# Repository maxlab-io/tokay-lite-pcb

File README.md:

# 

[Tokay Lite](https://maxlab.io/store/edge-ai-camera/) is the ESP32 camera development board ideal for low-power image
processing applications on the edge.

Tokay Lite can be used as standalone devkit to aid developers with a convinient
tool or be embedded in the bigger system to augument it with the vision and
image processing data.

## Tokay Lite Features

* ESP32-S3 chip compatible with TensorFlow Lite, enabling AI right in the device.
* OV2640 camera sensor delivering 15 fps @ 2MP.
* Ultra-low power design: programmable external RTC controls
  the entire power distribution, allowing the device to consume microamps during
  sleep.
* Motion detection with wake-up support.
* Nightvision mode with software-controlled IR filter to improve
  pictures during daytime.
* 10 IR LEDs to illuminate the scene.
* Ambient light sensor to intelligently select between day and night-time modes.
* Convenient 70mm x 70mm form factor.
* Embedded lithium battery charger and JST-PH battery connector.

## PCB Dimensions

Tokay LITE is packed into 70x70mm with M3 mounting holes at each corner,
as can be seen from a following drawing:

## Firmware

The Tokay AI Camera is powered by the ESP-IDF framework.

Check the [GitHub firmware repository]() for the source code
or [the camera documentation page](https://docs.maxlab.io/docs/edge-ai-tokay-lite/firmware/)
for more information on how to build an flash the firmware.

## KiCAD Dependencies

The Tokay PCB is made using [KiML](https://github.com/maxlab-io/kiml/),
the atomic components library from MAXLAB.

If you wish to modify the schematics or PCB you need to install KiML first.
Proceed to [the KiML installation guide](https://github.com/maxlab-io/kiml#how-to-install-kiml)
for further information.

## Ordering Samples

For information about ordering samples please proceed to [MAXLAB Tokay Lite product page](https://maxlab.io/store/edge-ai-camera/).

## License

The project is licensed under [the CERN Open Hardware Licence Version 2 - Permissive](./LICENSE.txt) terms.

## Business Inquiries or Questions

If you have the camera-related questions or inquiries, please drop us an email
on [hi@maxlab.io](mailto:hi@maxlab.io) or send us a message trough
[the Contact Us form](https://maxlab.io/contact/).

## Other Links

* [CADLAB.io](https://cadlab.io/project/27230). 
* [Hackaday](https://hackaday.io/project/189135-tokay-lite-multi-purpose-esp32-ai-camera)

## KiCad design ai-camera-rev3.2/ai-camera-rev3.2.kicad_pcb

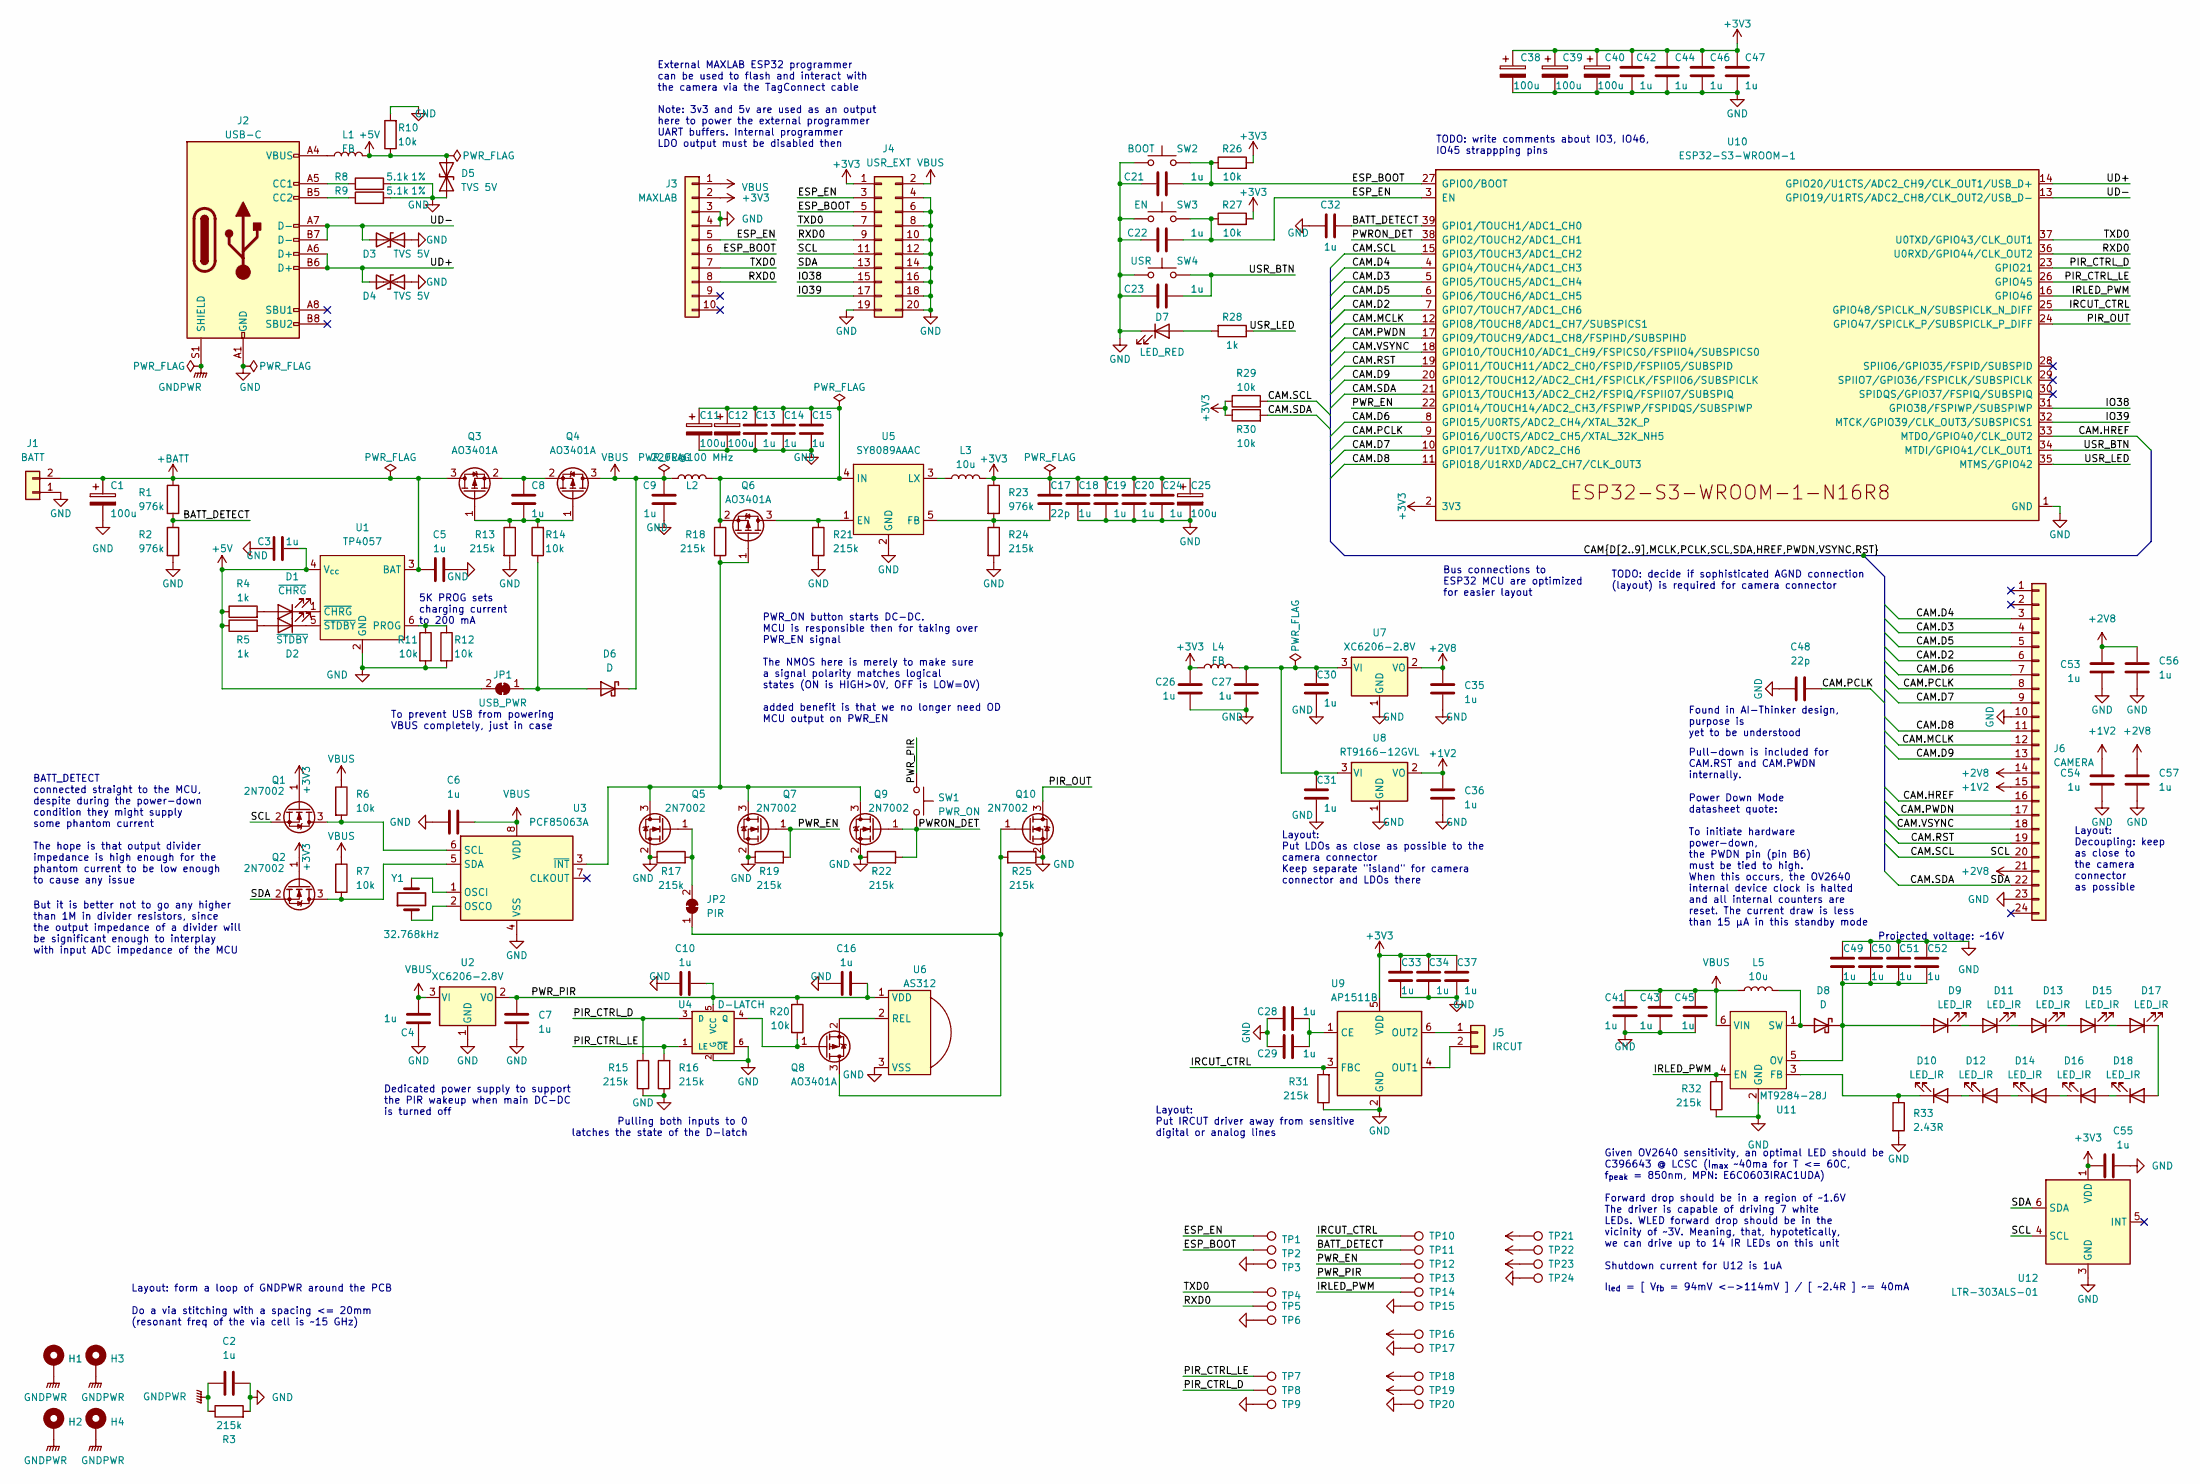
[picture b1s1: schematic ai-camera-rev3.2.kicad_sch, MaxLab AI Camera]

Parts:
C1, C11, C12, C25, C38, C39, C40: 100u_CASE-B-3528_TAJB107K006RNJ; CP_EIA-3528-15_AVX-H; Rating 6.3V; Tolerance 10%; MPN TAJB107K006RNJ
C2, C6, C10, C15, C16, C18, C21, C23, C28, C29, C32, C33, C45, C46, C47, C49, C54, C55, C56, C57: 10u_0402_CL05A105KA5NQNC; C_0402_1005Metric; Tolerance 10%; Rating 25V; MPN CL05A105KA5NQNC
C3, C4, C5, C7, C8, C9, C13, C14, C19, C20, C22, C24, C26, C27, C30, C31, C34, C35, C36, C37, C41, C42, C43, C44, C50, C51, C52, C53: 10u_0402_CL05A105KA5NQNC; C_0402_1005Metric; Rating 25V; Tolerance 10%; MPN CL05A105KA5NQNC
C17, C48: 22p_0402_0402CG220J500NT; C_0402_1005Metric; Rating 50V; Tolerance 5%; MPN 0402CG220J500NT
D1, D7: 0603_RED_KT-0603R; LED_0603_1608Metric; MPN KT-0603R
D2: 0603_GREEN_19-217/GHC-YR1S2/3T; LED_0603_1608Metric; MPN 19-217/GHC-YR1S2/3T
D3, D4, D5: SOD-523_BSD5C051L; D_SOD-523; MPN BSD5C051L
D6, D8: B5819W-SL_SOD-123; D_SOD-123; Rating 1A; MPN B5819W SL
D9, D10, D11, D12, D13, D14, D15, D16, D17, D18: 0603_IR_850nm_E6C0603IRAC1UDA; LED_0603_1608Metric; MPN E6C0603IRAC1UDA
H1, H2, H3, H4: MountingHole_Pad; MountingHole_3.2mm_M3_Pad_TopBottom
J1: Conn-01x02_P2mm_NONAME_JST-PH_C47647; JST_PH_S2B-PH-SM4-TB_1x02-1MP_P2.00mm_Horizontal; MPN C47647
J2: TYPE-C-31-M-12; USB_C_Receptacle_HRO_TYPE-C-31-M-12; MPN TYPE-C-31-M-12
J3: MAXLAB; Tag-Connect_TC2050-IDC-FP_2x05_P1.27mm_Vertical
J4: Conn-02x10_P2.54mm_B-2100S20P-B110; PinHeader_2x10_P2.54mm_Vertical; MPN B-2100S20P-B110
J5: Conn-01x02_P1.25mm_10114829-10102LF; 10114829-10102LF; MPN 10114829-10102LF
J6: Conn_01x24_FFC_0.5mm_AFC01-S24FCC-00; Jushuo_AFC01-S24FCC-00_1x24-1MP_P0.50_Horizontal; MPN AFC01-S24FCC-00
JP1: USB_PWR; SolderJumper-2_P1.3mm_Bridged2Bar_Pad1.0x1.5mm
JP2: PIR; SolderJumper-2_P1.3mm_Bridged2Bar_Pad1.0x1.5mm
L1, L2, L4: FB_2A_0805_220R@100MHz_BLM21PG221SN1D; L_0805_2012Metric_Pad1.15x1.40mm_HandSolder; Rating 2A; MPN BLM21PG221SN1D
L3, L5: 10u_1.5A_4x4mm_SWPA4030S100MT; L_Sunlord_SWPA40xxS; Rating 1.5A; MPN SWPA4030S100MT
Q1, Q2, Q5, Q7, Q9, Q10: 2N7002; SOT-23; MPN 2N7002
Q3, Q4, Q6, Q8: AO3401A; SOT-23; MPN AO3401A
R1, R2, R23: 976k_0402_0402WGD9763TCE; R_0402_1005Metric; Tolerance 0.5%; MPN 0402WGD9763TCE
R3, R13, R15, R16, R17, R18, R19, R21, R22, R24, R25, R31, R32: 215k_0402_0402WGD2153TCE; R_0402_1005Metric; Tolerance 0.5%; MPN 0402WGD2153TCE
R4, R5, R28: 1k_0402_0402WGF1001TCE; R_0402_1005Metric; Tolerance 1%; MPN 0402WGF1001TCE
R6, R7, R10, R11, R12, R14, R20, R26, R27, R29, R30: 10k_0402_0402WGF1002TCE; R_0402_1005Metric; Tolerance 1%; MPN 0402WGF1002TCE
R8, R9: 5.1k_0603_0603WAF5101T5E; R_0603_1608Metric; Tolerance 1%; MPN 0603WAF5101T5E
R33: 2.43R_0805_0805W8F243KT5E; R_0805_2012Metric; Tolerance 1%; MPN 0805W8F243KT5E
SW1, SW4: SW_PB_90deg_K2-1102AQ-H4CW-01; MPN K2-1102AQ-N4CW-01
SW2, SW3: SW_PB_TS-1187A-B-A-B; SW_SPST_TL3342; MPN TS-1187A-B-A-B
TP1, TP2, TP3, TP4, TP5, TP6, TP7, TP8, TP9, TP10, TP11, TP12, TP13, TP14, TP15, TP16, TP17, TP18, TP19, TP20, TP21, TP22, TP23, TP24: TestPoint; TestPoint_Pad_D1.0mm
U1: TP4057-42-SOT26-R; SOT-23-6; MPN TP4057-42-SOT26-R
U2, U7: XC6206-2.8V; SOT-23; MPN XC6206-2.8V
U3: PCF85063AT; SO-8_3.9x4.9mm_P1.27mm; MPN PCF85063AT/AAZ
U4: TI_SN74LVC1G373DBVR; SOT-23-6; MPN SN74LVC1G373DBVR
U5: SY8089AAAC; SOT-23-5; MPN SY8089AAAC
U6: PIR_AS312; AS312; MPN AS312
U8: RT9166-12GVL; SOT-23; MPN RT9166-12GVL
U9: AP1511B; SOT-23-6; MPN AP1511B
U10: ESP32-S3-WROOM-1-N16R8; ESP32-S3-WROOM-1; MPN ESP32-S3-WROOM-1-N16R8
U11: MT9284-28J; SOT-23-6; MPN MT9284-28J
U12: LTR-303ALS-01; Lite-On_LTR-303ALS-01; MPN LTR-303ALS-01
Y1: 32.768kHz_Q13FC1350000400; Crystal_SMD_3215-2Pin_3.2x1.5mm; MPN Q13FC1350000400

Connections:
+1V2: C36.1, C54.2, J6.15, TP16.1, U8.2 (VO)
+2V8: C35.1, C53.1, C56.2, C57.2, J6.14, J6.21, TP18.1, U7.2 (VO)
+3V3: C17.1, C18.2, C19.2, C20.2, C24.2, C25.1, C26.1, C33.2, C34.2, C37.2, C38.1, C39.1, C40.1, C42.1, C44.1, C46.1, C47.1, C55.1, J3.2, J4.1, L3.2, L4.1, Q1.1 (G), Q2.1 (G), R23.1, R26.2, R27.2, R29.1, R30.1, TP22.1, U9.5 (VDD), U10.2 (3V3), U12.1 (VDD)
+5V: C3.2, D5.2 (A2), JP1.2 (B), L1.2, R4.1, R5.1, R10.1, TP23.1, U1.4 (V_{cc})
+BATT: C1.1, C5.1, J1.2, Q3.3 (D), R1.1, TP19.1, U1.3 (BAT)
/BATT_DETECT: C32.1, R1.2, R2.1, TP11.1, U10.39 (GPIO1/TOUCH1/ADC1_CH0)
/CAM.D2: J6.6, U10.7 (GPIO7/TOUCH7/ADC1_CH6)
/CAM.D3: J6.4, U10.5 (GPIO5/TOUCH5/ADC1_CH4)
/CAM.D4: J6.3, U10.4 (GPIO4/TOUCH4/ADC1_CH3)
/CAM.D5: J6.5, U10.6 (GPIO6/TOUCH6/ADC1_CH5)
/CAM.D6: J6.7, U10.8 (GPIO15/U0RTS/ADC2_CH4/XTAL_32K_P)
/CAM.D7: J6.9, U10.10 (GPIO17/U1TXD/ADC2_CH6)
/CAM.D8: J6.11, U10.11 (GPIO18/U1RXD/ADC2_CH7/CLK_OUT3)
/CAM.D9: J6.13, U10.20 (GPIO12/TOUCH12/ADC2_CH1/FSPICLK/FSPIIO6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)
/CAM.HREF: J6.16, U10.33 (MTDO/GPIO40/CLK_OUT2)
/CAM.MCLK: J6.12, U10.12 (GPIO8/TOUCH8/ADC1_CH7/SUBSPICS1)
/CAM.PCLK: C48.1, J6.8, U10.9 (GPIO16/U0CTS/ADC2_CH5/XTAL_32K_NH5)
/CAM.PWDN: J6.17, U10.17 (GPIO9/TOUCH9/ADC1_CH8/FSPIHD/SUBSPIHD)
/CAM.RST: J6.19, U10.19 (GPIO11/TOUCH11/ADC2_CH0/FSPID/FSPIIO5/S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)
/CAM.SCL: J4.11, J6.20, Q1.2 (S), R29.2, U10.15 (GPIO3/TOUCH3/ADC1_CH2), U12.4 (SCL)
/CAM.SDA: J4.13, J6.22, Q2.2 (S), R30.2, U10.21 (GPIO13/TOUCH13/ADC2_CH2/FSPIQ/FSPIIO7/S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), U12.6 (SDA)
/CAM.VSYNC: J6.18, U10.18 (GPIO10/TOUCH10/ADC1_CH9/FSPICS0/FSPIIO4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)
/ESP_BOOT: C21.2, J3.6, J4.5, R26.1, SW2.2, TP2.1, U10.27 (GPIO0/BOOT)
/ESP_EN: C22.2, J3.5, J4.3, R27.1, SW3.2, TP1.1, U10.3 (EN)
/IO38: J4.15, U10.31 (GPIO38/FSPIWP/SUBSPIWP)
/IO39: J4.17, U10.32 (MTCK/GPIO39/CLK_OUT3/SUBSPICS1)
/IRCUT_CTRL: R31.2, TP10.1, U9.3 (FBC), U10.25 (GPIO48/SPICLK_N/SUBSPICLK_N_DIFF)
/IRLED_PWM: R32.2, TP14.1, U10.16 (GPIO46), U11.4 (EN)
/PIR_CTRL_D: R15.2, TP8.1, U4.3 (D), U10.23 (GPIO21)
/PIR_CTRL_LE: R16.2, TP7.1, U4.1 (LE), U10.26 (GPIO45)
/PIR_OUT: Q10.3 (D), U10.24 (GPIO47/SPICLK_P/SUBSPICLK_P_DIFF)
/PWRON_DET: Q9.1 (G), R22.2, SW1.2, U10.38 (GPIO2/TOUCH2/ADC1_CH1)
/PWR_EN: Q7.1 (G), R19.2, TP12.1, U10.22 (GPIO14/TOUCH14/ADC2_CH3/FSPIWP/FSPIDQS/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)
/PWR_PIR: C7.1, C10.1, C16.1, R20.1, SW1.1, TP13.1, U2.2 (VO), U4.5 (VCC), U6.1 (VDD)
/RXD0: J3.8, J4.9, TP5.1, U10.36 (U0RXD/GPIO44/CLK_OUT2)
/TXD0: J3.7, J4.7, TP4.1, U10.37 (U0TXD/GPIO43/CLK_OUT1)
/UD+: D4.2 (A2), J2.A6 (D+), J2.B6 (D+), U10.14 (GPIO20/U1CTS/ADC2_CH9/CLK_OUT1/USB_D+)
/UD-: D3.2 (A2), J2.A7 (D-), J2.B7 (D-), U10.13 (GPIO19/U1RTS/ADC2_CH8/CLK_OUT2/USB_D-)
/USR_BTN: C23.2, SW4.2, U10.34 (MTDI/GPIO41/CLK_OUT1)
/USR_LED: R28.1, U10.35 (MTMS/GPIO42)
GND: C1.2, C2.1, C3.1, C4.1, C5.2, C6.2, C7.2, C9.1, C10.2, C11.2, C12.2, C13.1, C14.2, C15.1, C16.2, C18.1, C19.1, C20.1, C21.1, C22.1, C23.1, C24.1, C25.2, C26.2, C27.2, C28.2, C29.2, C30.2, C31.2, C32.2, C33.1, C34.1, C35.2, C36.2, C37.1, C38.2, C39.2, C40.2, C41.1, C42.2, C43.2, C44.2, C45.1, C46.2, C47.2, C48.2, C49.2, C50.1, C51.1, C52.1, C53.2, C54.1, C55.2, C56.1, C57.1, D3.1 (A1), D4.1 (A1), D5.1 (A1), D7.1 (K), J1.1, J2.A1 (GND), J2.A12 (GND), J2.B1 (GND), J2.B12 (GND), J3.3, J3.4, J4.4, J4.6, J4.8, J4.10, J4.12, J4.14, J4.16, J4.18, J4.19, J4.20, J6.10, J6.23, Q5.2 (S), Q7.2 (S), Q9.2 (S), Q10.2 (S), R2.2, R3.2, R8.2, R9.2, R10.2, R11.2, R12.2, R13.2, R15.1, R16.1, R17.1, R19.1, R21.2, R22.1, R24.2, R25.1, R31.1, R32.1, R33.2, SW2.1, SW3.1, SW4.1, TP3.1, TP6.1, TP9.1, TP15.1, TP17.1, TP20.1, TP24.1, U1.2 (GND), U2.1 (GND), U3.4 (VSS), U4.2 (G), U4.6 (~OE), U5.2 (GND), U6.3 (VSS), U7.1 (GND), U8.1 (GND), U9.2 (GND), U10.1 (GND), U10.40 (GND), U10.41 (GND), U11.2 (GND), U12.3 (GND)
GNDPWR: C2.2, H1.1, H2.1, H3.1, H4.1, J2.S1 (SHIELD), R3.1
unnamed: D1.2 (A), R4.2
unnamed: D1.1 (K), U1.1 (~CHRG)
unnamed: D2.2 (A), R5.2
unnamed: D2.1 (K), U1.5 (~STDBY)
unnamed: D6.2 (A), JP1.1 (A), R14.1
unnamed: D7.2 (A), R28.2
unnamed: D8.2 (A), L5.2, U11.1 (SW)
unnamed: C49.1, C50.2, C51.2, C52.2, D8.1 (K), D9.2 (A), U11.5 (OV)
unnamed: D10.2 (A), D12.1 (K)
unnamed: D10.1 (K), R33.1, U11.3 (FB)
unnamed: D9.1 (K), D11.2 (A)
unnamed: D11.1 (K), D13.2 (A)
unnamed: D12.2 (A), D14.1 (K)
unnamed: D13.1 (K), D15.2 (A)
unnamed: D14.2 (A), D16.1 (K)
unnamed: D15.1 (K), D17.2 (A)
unnamed: D16.2 (A), D18.1 (K)
unnamed: D17.1 (K), D18.2 (A)
unnamed: J2.A5 (CC1), R8.1
unnamed: J2.B5 (CC2), R9.1
unnamed: J2.A4 (VBUS), J2.A9 (VBUS), J2.B4 (VBUS), J2.B9 (VBUS), L1.1
unnamed: J5.1, U9.6 (OUT2)
unnamed: J5.2, U9.4 (OUT1)
unnamed: JP2.1 (A), Q8.3 (D), Q10.1 (G), R25.2
unnamed: JP2.2 (B), Q5.1 (G), R17.2
unnamed: Q1.3 (D), R6.2, U3.6 (SCL)
unnamed: Q2.3 (D), R7.2, U3.5 (SDA)
unnamed: C8.1, Q3.1 (G), Q4.1 (G), R13.1, R14.2
unnamed: C8.2, Q3.2 (S), Q4.2 (S)
unnamed: Q5.3 (D), Q6.1 (G), Q7.3 (D), Q9.3 (D), R18.2, U3.3 (~INT)
unnamed: Q6.3 (D), R21.1, U5.1 (EN)
unnamed: C11.1, C12.1, C13.2, C14.1, C15.2, L2.2, Q6.2 (S), R18.1, U5.4 (IN)
unnamed: Q8.1 (G), R20.2, U4.4 (Q)
unnamed: Q8.2 (S), U6.2 (REL)
unnamed: R11.1, R12.1, U1.6 (PROG)
unnamed: U3.1 (OSCI), Y1.2
unnamed: U3.2 (OSCO), Y1.1
unnamed: C17.2, R23.2, R24.1, U5.5 (FB)
unnamed: L3.1, U5.3 (LX)
unnamed: C27.1, C30.1, C31.1, L4.2, U7.3 (VI), U8.3 (VI)
unnamed: C28.1, C29.1, U9.1 (CE)
VBUS: C4.2, C6.1, C9.2, C41.2, C43.1, C45.2, D6.1 (K), J3.1, J4.2, L2.1, L5.1, Q4.3 (D), R6.1, R7.1, TP21.1, U2.3 (VI), U3.8 (VDD), U11.6 (VIN)

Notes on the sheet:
Found in AI-Thinker design, purpose is yet to be understood
External MAXLAB ESP32 programmer can be used to flash and interact with the camera via the TagConnect cable
I_{led} = [ V_{fb} = 94mV <->114mV ] / [ ~2.4R ] ~= 40mA
But it is better not to go any higher than 1M in divider resistors, since the output impedance of a divider will be significant enough to interplay with input ADC impedance of the MCU
Pulling both inputs to 0 latches the state of the D-latch
Note: 3v3 and 5v are used as an output here to power the external programmer UART buffers. Internal programmer LDO output must be disabled then
Layout: Put IRCUT driver away from sensitive digital or analog lines
Layout: form a loop of GNDPWR around the PCB Do a via stitching with a spacing <= 20mm (resonant freq of the via cell is ~15 GHz)
Pull-down is included for CAM.RST and CAM.PWDN internally.
TODO: write comments about IO3, IO46, IO45 strappping pins
Bus connections to ESP32 MCU are optimized for easier layout
To prevent USB from powering VBUS completely, just in case
PWR_ON button starts DC-DC. MCU is responsible then for taking over PWR_EN signal The NMOS here is merely to make sure a signal polarity matches logical states (ON is HIGH>0V, OFF is LOW=0V) added benefit is that we no longer need OD MCU output on PWR_EN
Power Down Mode datasheet quote: To initiate hardware power-down, the PWDN pin (pin B6) must be tied to high. When this occurs, the OV2640 internal device clock is halted and all internal counters are reset. The current draw is less than 15 µA in this standby mode
Layout: Put LDOs as close as possible to the camera connector Keep separate "island" for camera connector and LDOs there
TODO: decide if sophisticated AGND connection (layout) is required for camera connector
5K PROG sets charging current to 200 mA
Given OV2640 sensitivity, an optimal LED should be C396643 @ LCSC (I_{max} ~40ma for T <= 60C, f_{peak} = 850nm, MPN: E6C0603IRAC1UDA) Forward drop should be in a region of ~1.6V The driver is capable of driving 7 white LEDs. WLED forward drop should be in the vicinity of ~3V. Meaning, that, hypote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
BATT_DETECT connected straight to the MCU, despite during the power-down condition they might supply some phantom current The hope is that output divider impedance is high enough for the phantom current to be low enough to cause any issue
Dedicated power supply to support the PIR wakeup when main DC-DC is turned off
Projected voltage: ~16V
Layout: Decoupling: keep as close to the camera connector as possible

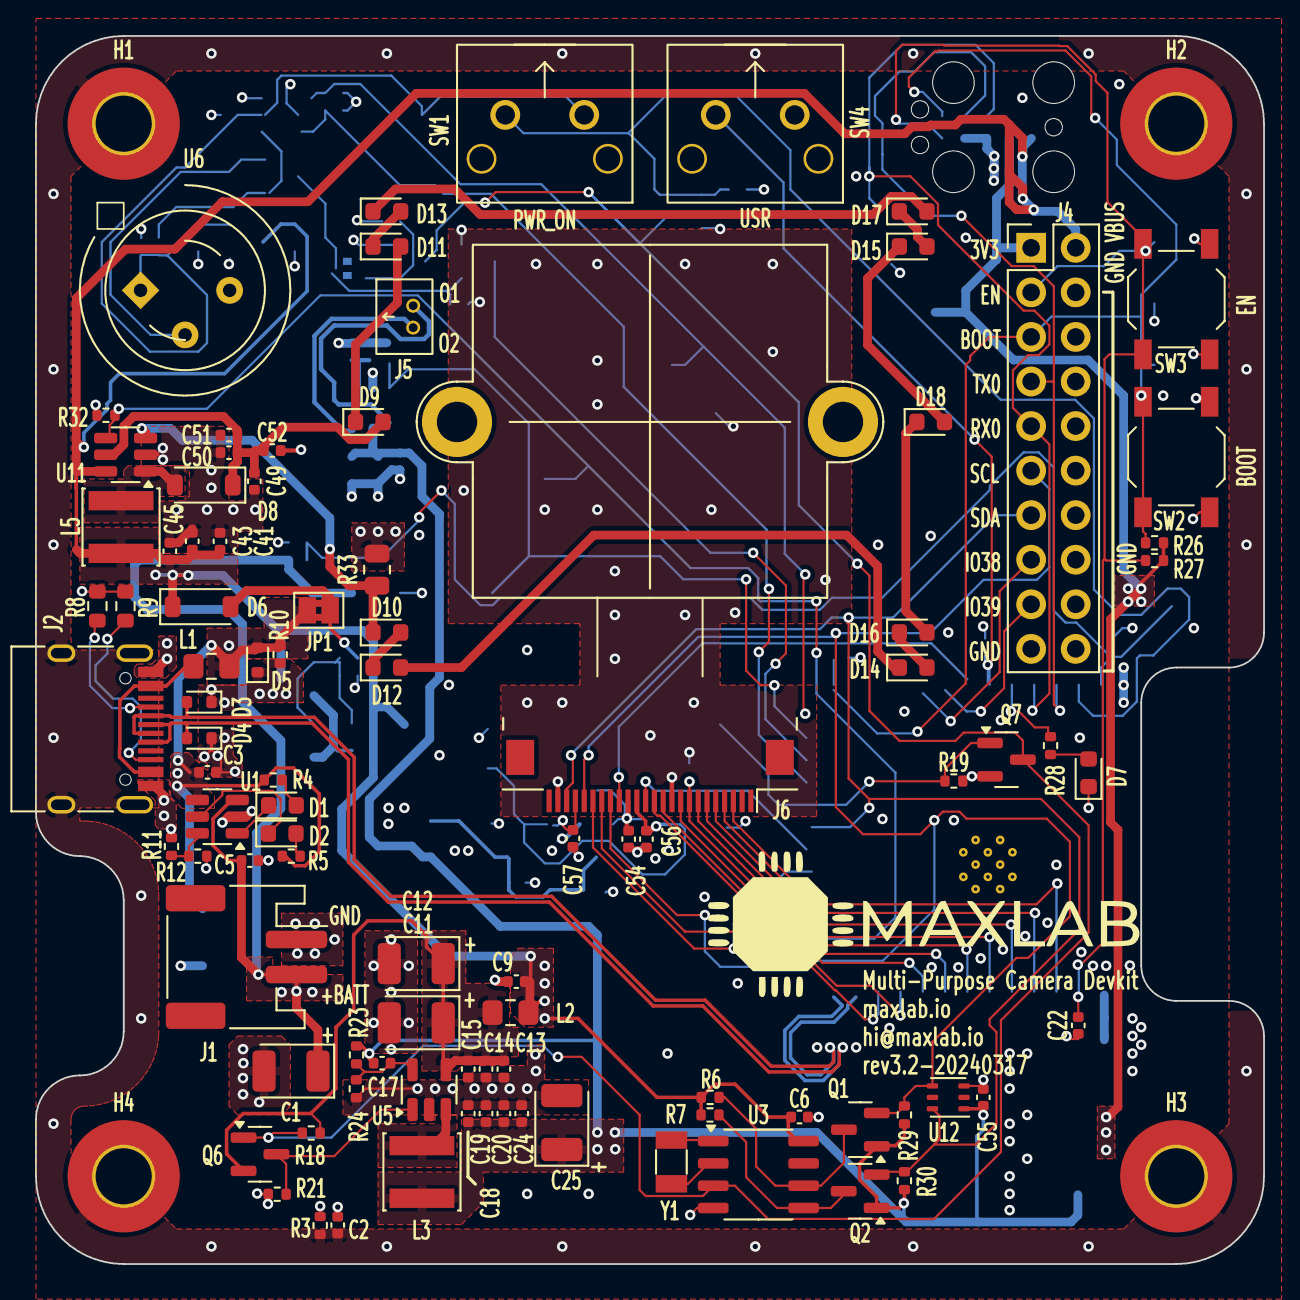
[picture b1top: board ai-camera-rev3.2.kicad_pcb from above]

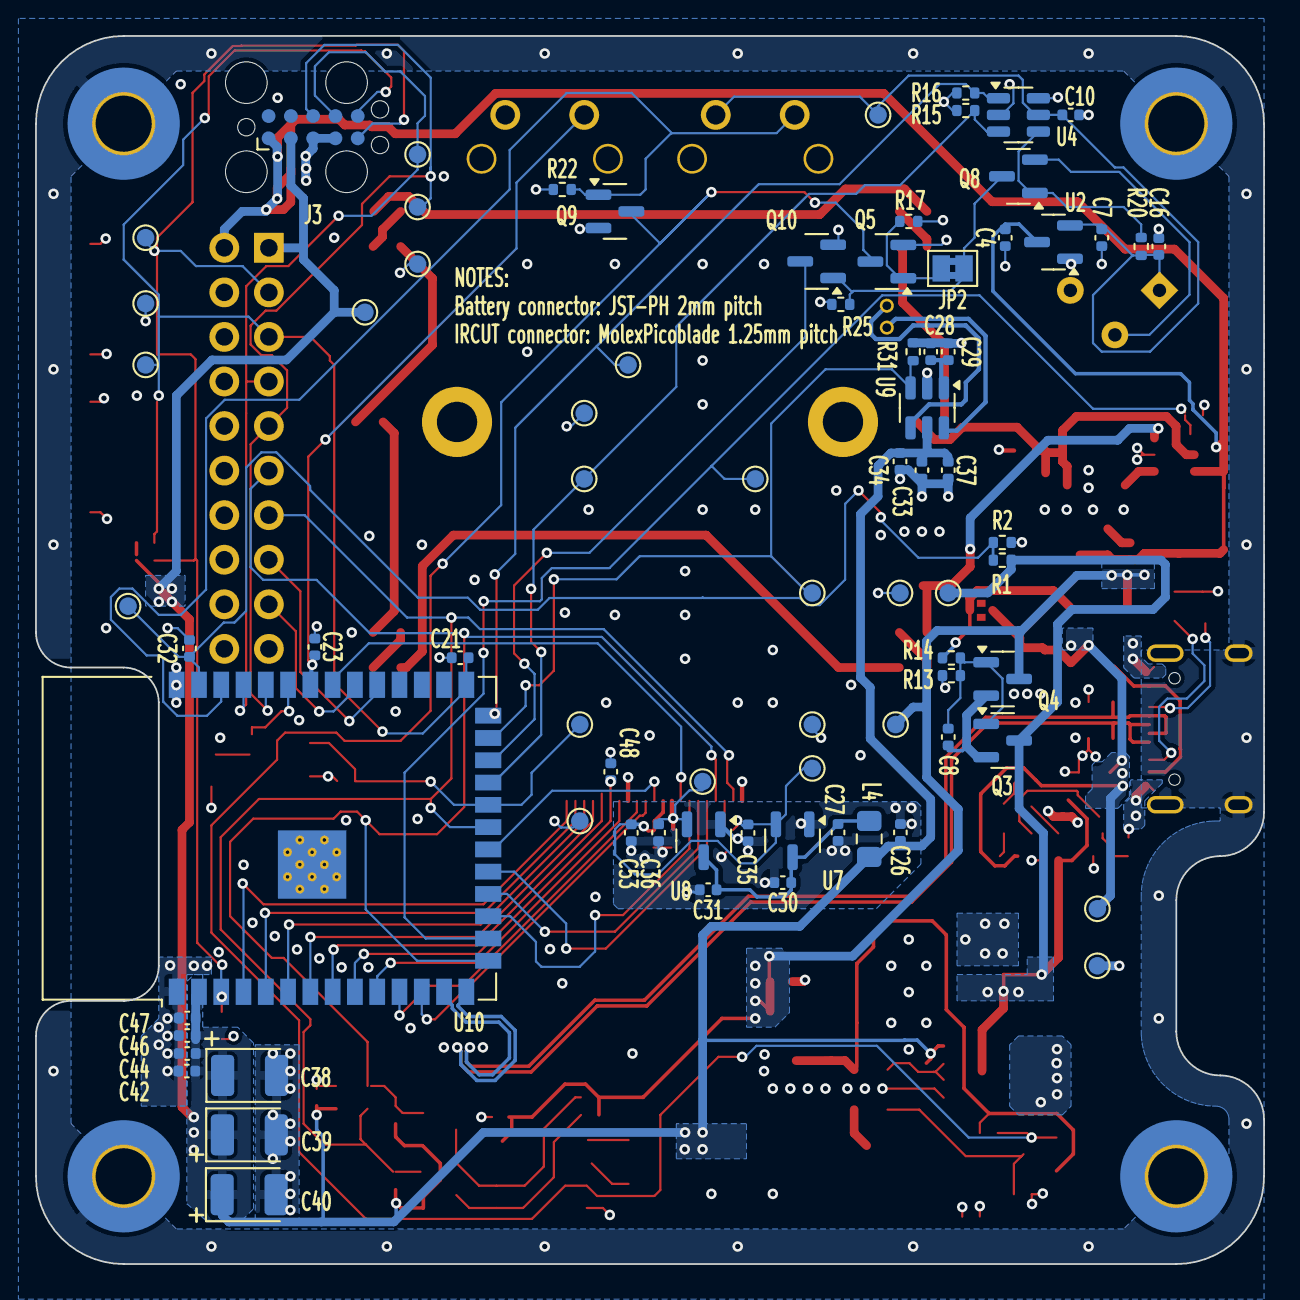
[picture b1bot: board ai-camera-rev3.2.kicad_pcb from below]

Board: 4 copper layers, 70.0 x 70.0 mm, 176 parts (78 on the bottom side), 84 nets.

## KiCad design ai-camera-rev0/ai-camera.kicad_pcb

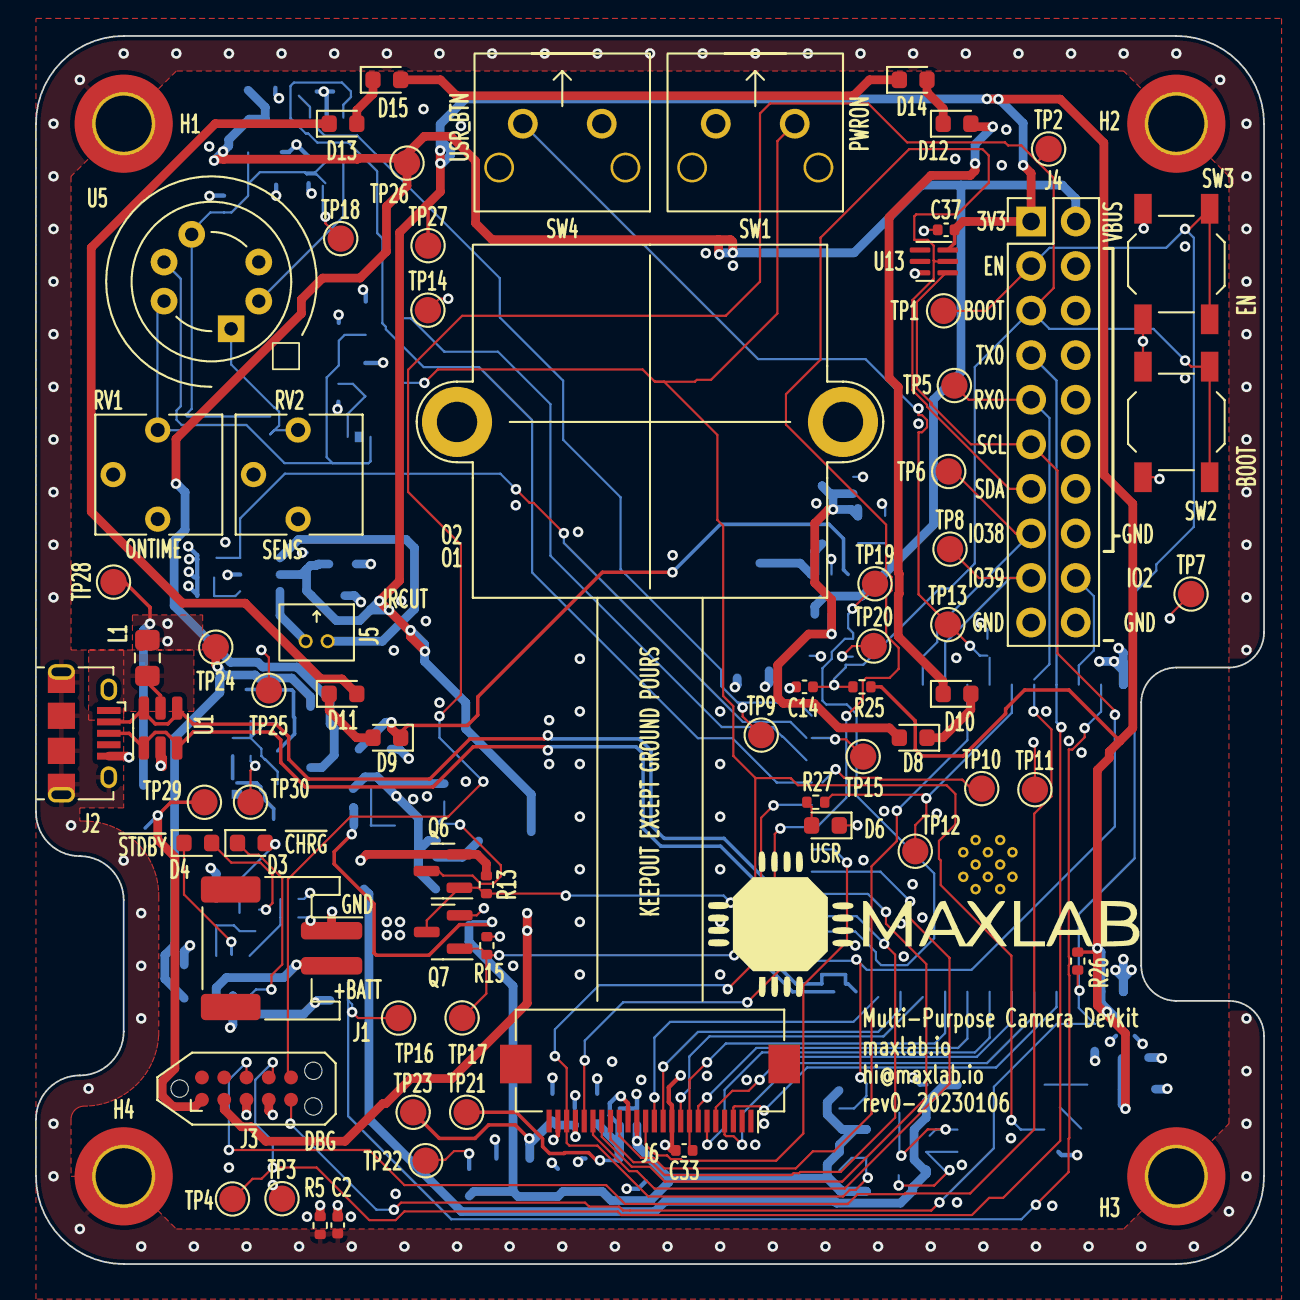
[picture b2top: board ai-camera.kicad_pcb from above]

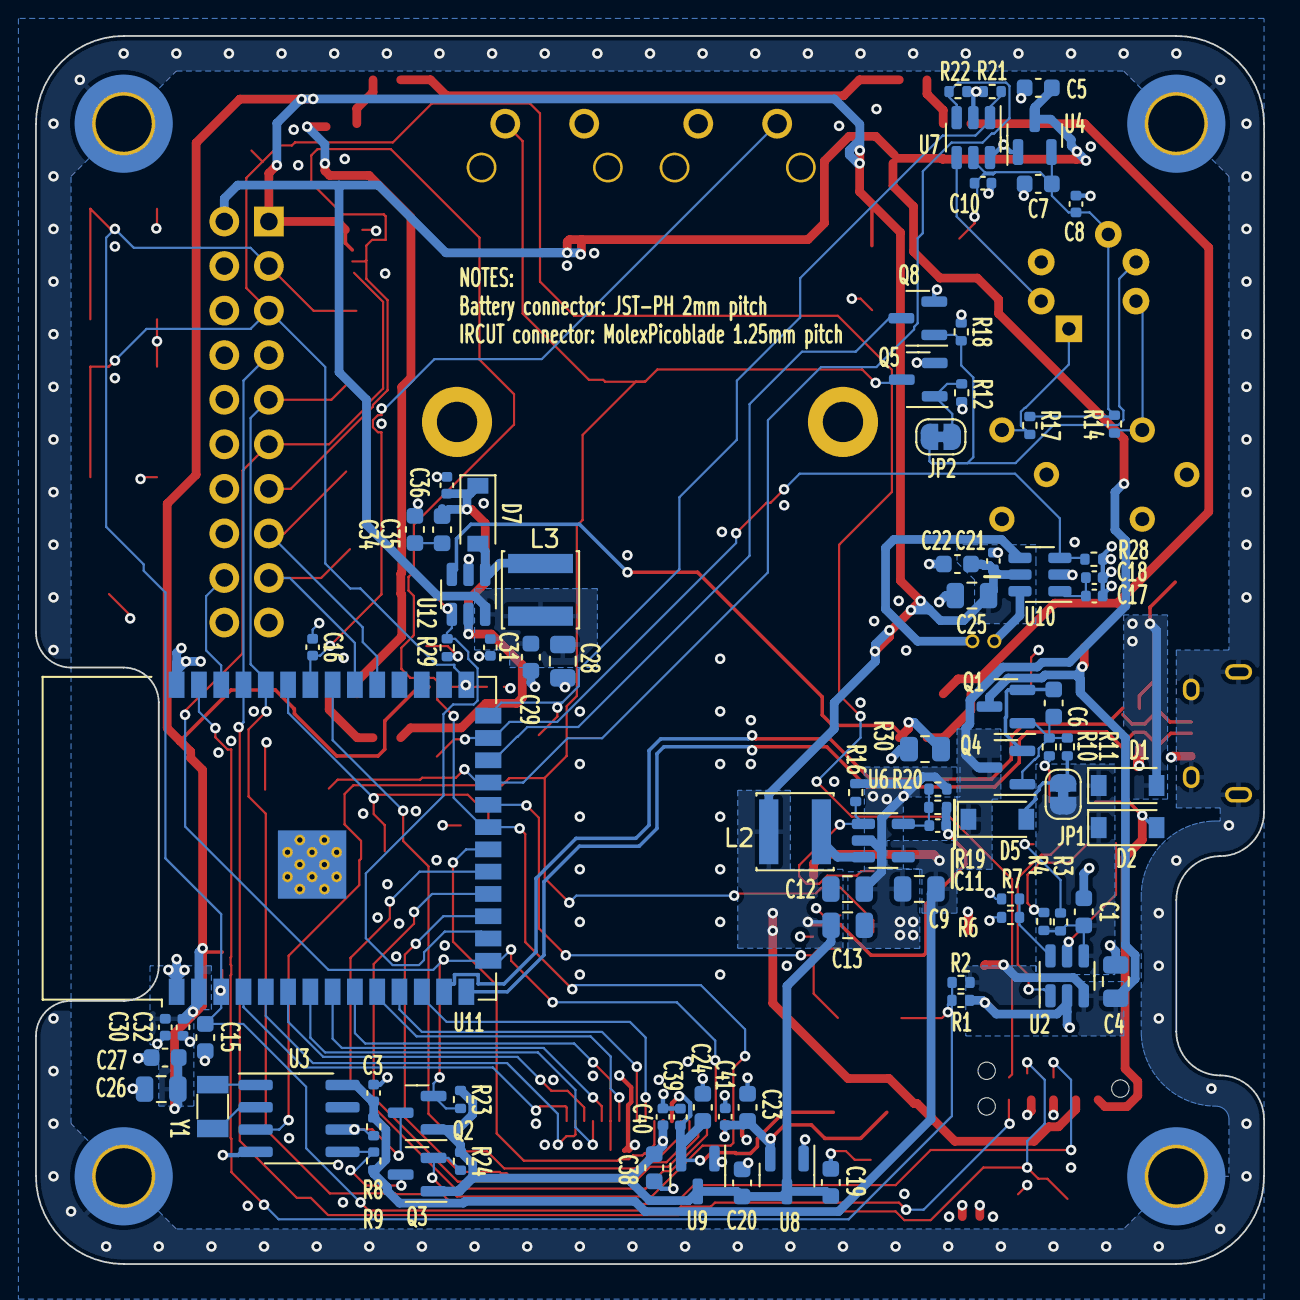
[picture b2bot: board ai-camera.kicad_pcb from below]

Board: 4 copper layers, 70.0 x 70.0 mm, 159 parts (86 on the bottom side), 82 nets.

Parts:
C1, C5, C6, C7, C15, C19, C20, C22, C23, C24, C27, C29, C34, C35, C38: 10u_0603_CL10A106MA8NRNC; C_0603_1608Metric
C2, C3, C8, C10, C14, C16, C17, C18, C21, C30, C31, C32, C36, C37, C39, C40, C41: 100n_0402_CL05B104KB54PNC; C_0402_1005Metric
C4, C9, C12, C13, C25, C26, C28: 22u_0805_CL21A226MAQNNNE; C_0805_2012Metric
C11, C33: 22p_0402_0402CG220J500NT; C_0402_1005Metric
D1, D2, D5, D7: B5819W-SL_SOD-123; D_SOD-123
D3, D6: 0603_RED_KT-0603R; LED_0603_1608Metric
D4: 0603_GREEN_19-217/GHC-YR1S2/3T; LED_0603_1608Metric
D8, D9, D10, D11, D12, D13, D14, D15: 0603_IR_850nm_E6C0603IRAC1UDA; LED_0603_1608Metric
H1, H2, H3, H4: M3; MountingHole_3.2mm_M3_DIN965_Pad_TopBottom
J1: Conn-01x02_P2mm_NONAME_JST-PH_C47647; JST_PH_S2B-PH-SM4-TB_1x02-1MP_P2.00mm_Horizontal
J2: USB_B_Micro_10118194-0001LF; USB_Micro-B_Amphenol_10118194_Horizontal
J3: DBG; Tag-Connect_TC2050-IDC-NL_2x05_P1.27mm_Vertical
J4: Conn-02x10_P2.54mm_B-2100S20P-B110; PinHeader_2x10_P2.54mm_Vertical
J5: Conn-01x02_P1.25mm_10114829-10102LF; 10114829-10102LF
J6: Conn_01x24_FFC_0.5mm_hirose_FH12-24S-0.5SH; Hirose_FH12-24S-0.5SH_1x24-1MP_P0.50mm_Horizontal
JP1: CUT_USB; SolderJumper-2_P1.3mm_Bridged_RoundedPad1.0x1.5mm
JP2: CUT_PIR; SolderJumper-2_P1.3mm_Bridged_RoundedPad1.0x1.5mm
L1: 0805_FB_220R@100MHz_BLM21PG221SN1D; L_0805_2012Metric_Pad1.15x1.40mm_HandSolder
L2, L3: 10u_SWPA4030S100MT; L_Sunlord_SWPA40xxS
Q1, Q4, Q6: AO3401A; SOT-23
Q2, Q3, Q5, Q7, Q8: AO3400A; SOT-23
R1, R2, R14, R17, R19: 976k_0402_0402WGD9763TCE; R_0402_1005Metric
R3, R4, R27: 1k_0402_0402WGF1001TCE; R_0402_1005Metric
R5, R10, R12, R13, R15, R16, R18, R20, R21, R22, R28, R29: 215k_0402_0402WGD2153TCE; R_0402_1005Metric
R6, R7, R8, R9, R11, R23, R24, R25, R26: 10k_0402_0402WGF1002TCE; R_0402_1005Metric
R30: 2.5R_0805_AR05FTCW2R50; R_0805_2012Metric
RV1, RV2: 1M_3362P-1-105; Potentiometer_Vishay_T73YP_Vertical
SW1, SW4: SW_PB_90deg_K2-1102AQ-H4CW-01
SW2, SW3: SW_PB_TS-1187A-B-A-B; SW_SPST_TL3342
TP1, TP2, TP3, TP4, TP5, TP6, TP7, TP8, TP9, TP10, TP11, TP12, TP13, TP14, TP15, TP16, TP17, TP18, TP19, TP20, TP21, TP22, TP23, TP24, TP25, TP26, TP27, TP28, TP29, TP30: TP; TestPoint_Pad_D1.5mm
U1: SRV05-4; SOT-23-6
U2: TP4057-42-SOT26-R; SOT-23-6
U3: PCF8563T/5,518; SOIC-8_3.9x4.9mm_P1.27mm
U4, U8: XC6206-2.8V; SOT-23
U5: PIR_BS612; BS612
U6: SY8089AAAC; SOT-23-5
U7: SOT-23-6_SN74LVC1G373DBVR_TI; SOT-23-6
U9: RT9166-12GVL; SOT-23
U10: AP1511B; SOT-23-6
U11: ESP32-S3-WROOM-1-N16R8; ESP32-S3-WROOM-1
U12: MT9284-28J; SOT-23-6
U13: APDS-9306-065; Broadcom_DFN-6_2x2mm_P0.65mm
Y1: 32.768kHz_Q13FC1350000400; Crystal_SMD_3215-2Pin_3.2x1.5mm

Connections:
+1V2: C24.1, C39.2, J6.15, TP21.1, U9.2 (VO)
+2V8: C23.1, C41.2, J6.21, TP23.1, U8.2 (VO)
+3V3: C11.1, C12.1, C13.1, C19.1, C20.1, C21.2, C22.2, C25.2, C26.1, C27.1, C30.1, C32.1, C37.1, C38.1, C40.2, J3.2, J4.1, J6.14, L2.2, Q2.1 (G), Q3.1 (G), R19.1, R23.1, R24.1, R25.2, R26.2, TP27.1, U8.3 (VI), U9.3 (VI), U10.5 (VDD), U11.2 (3V3), U13.3 (VDD)
+5F: D1.2 (A), L1.2, TP28.1
+5P: D2.2 (A), J3.1, TP29.1
+BATT: C4.1, J1.2, Q1.3 (D), R1.1, TP24.1, U2.3 (BAT)
/BATT_DETECT: R1.2, R2.1, TP16.1, U11.39 (GPIO1/TOUCH1/ADC1_CH0)
/CAM.D2: J6.6, U11.7 (GPIO7/TOUCH7/ADC1_CH6)
/CAM.D3: J6.4, U11.5 (GPIO5/TOUCH5/ADC1_CH4)
/CAM.D4: J6.3, U11.4 (GPIO4/TOUCH4/ADC1_CH3)
/CAM.D5: J6.5, U11.6 (GPIO6/TOUCH6/ADC1_CH5)
/CAM.D6: J6.7, U11.8 (GPIO15/U0RTS/ADC2_CH4/XTAL_32K_P)
/CAM.D7: J6.9, U11.10 (GPIO17/U1TXD/ADC2_CH6)
/CAM.D8: J6.11, U11.11 (GPIO18/U1RXD/ADC2_CH7/CLK_OUT3)
/CAM.D9: J6.13, U11.20 (GPIO12/TOUCH12/ADC2_CH1/FSPICLK/FSPIIO6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)
/CAM.HREF: J6.16, U11.33 (MTDO/GPIO40/CLK_OUT2)
/CAM.MCLK: J6.12, U11.12 (GPIO8/TOUCH8/ADC1_CH7/SUBSPICS1)
/CAM.PCLK: C33.1, J6.8, U11.9 (GPIO16/U0CTS/ADC2_CH5/XTAL_32K_NH5)
/CAM.PWDN: J6.17, U11.17 (GPIO9/TOUCH9/ADC1_CH8/FSPIHD/SUBSPIHD)
/CAM.RST: J6.19, U11.19 (GPIO11/TOUCH11/ADC2_CH0/FSPID/FSPIIO5/S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)
/CAM.SCL: J4.11, J6.20, Q2.2 (S), R23.2, U11.15 (GPIO3/TOUCH3/ADC1_CH2), U13.1 (SCL)
/CAM.SDA: J4.13, J6.22, Q3.2 (S), R24.2, U11.21 (GPIO13/TOUCH13/ADC2_CH2/FSPIQ/FSPIIO7/S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), U13.2 (SDA)
/CAM.VSYNC: J6.18, U11.18 (GPIO10/TOUCH10/ADC1_CH9/FSPICS0/FSPIIO4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)
/ESP_BOOT: C14.2, J3.6, J4.5, R25.1, SW2.2, TP2.1, U11.27 (GPIO0/BOOT)
/ESP_EN: C15.2, J3.5, J4.3, R26.1, SW3.2, TP1.1, U11.3 (EN)
/IO2: J4.18, U11.38 (GPIO2/TOUCH2/ADC1_CH1)
/IO38: J4.15, TP6.1, U11.31 (GPIO38/FSPIWP/SUBSPIWP)
/IO39: J4.17, TP8.1, U11.32 (MTCK/GPIO39/CLK_OUT3/SUBSPICS1)
/IRCUT_CTRL: R28.2, TP15.1, U10.3 (FBC), U11.25 (GPIO48/SPICLK_N/SUBSPICLK_N_DIFF)
/IRLED_PWM: R29.2, TP19.1, U11.16 (GPIO46), U12.4 (EN)
/PIR_CTRL_D: R22.2, TP10.1, U7.3 (D), U11.23 (GPIO21)
/PIR_CTRL_LE: R21.2, TP9.1, U7.1 (LE), U11.26 (GPIO45)
/PIR_OUT: Q8.3 (D), U11.24 (GPIO47/SPICLK_P/SUBSPICLK_P_DIFF)
/PWR_EN: Q7.1 (G), R15.2, TP17.1, U11.22 (GPIO14/TOUCH14/ADC2_CH3/FSPIWP/FSPIDQS/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)
/PWR_PIR: C7.1, C8.1, C10.1, R14.1, R17.1, TP18.1, U4.2 (VO), U5.4 (VDD), U7.5 (VCC)
/RXD0: J3.8, J4.9, TP5.1, U11.36 (U0RXD/GPIO44/CLK_OUT2)
/TXD0: J3.7, J4.7, TP4.1, U11.37 (U0TXD/GPIO43/CLK_OUT1)
/UD+: J2.3 (D+), U1.1 (IO1), U1.3 (IO2), U11.14 (GPIO20/U1CTS/ADC2_CH9/CLK_OUT1/USB_D+)
/UD-: J2.2 (D-), U1.4 (IO3), U1.6 (IO4), U11.13 (GPIO19/U1RTS/ADC2_CH8/CLK_OUT2/USB_D-)
/USR_BTN: C16.2, SW4.2, TP13.1, U11.34 (MTDI/GPIO41/CLK_OUT1)
/USR_LED: R27.1, TP12.1, U11.35 (MTMS/GPIO42)
GND: C1.1, C2.1, C3.2, C4.2, C5.1, C7.2, C8.2, C9.2, C10.2, C12.2, C13.2, C14.1, C15.1, C16.1, C17.2, C18.2, C19.2, C20.2, C21.1, C22.1, C23.2, C24.2, C25.1, C26.2, C27.2, C28.1, C29.1, C30.2, C31.1, C32.2, C33.2, C34.1, C36.1, C37.2, C38.2, C39.1, C40.1, C41.1, D6.1 (K), J1.1, J2.5 (GND), J3.3, J3.4, J4.4, J4.6, J4.8, J4.10, J4.12, J4.14, J4.16, J4.19, J4.20, J6.10, J6.23, Q5.2 (S), Q7.2 (S), Q8.2 (S), R2.2, R5.2, R6.2, R7.2, R10.2, R12.1, R15.1, R16.2, R18.1, R20.2, R21.1, R22.1, R28.1, R29.1, R30.1, RV1.2, RV1.3, RV2.2, RV2.3, SW1.2, SW2.1, SW3.1, SW4.1, TP3.1, TP7.1, TP11.1, TP14.1, TP20.1, TP22.1, TP25.1, TP30.1, U1.2 (VN), U2.2 (GND), U3.4 (VSS), U4.1 (GND), U5.3 (VSS), U6.2 (GND), U7.2 (G), U7.6 (~OE), U8.1 (GND), U9.1 (GND), U10.2 (GND), U11.1 (GND), U11.40 (GND), U11.41 (GND), U12.2 (GND), U13.6 (GND)
GNDPWR: C2.2, H1.1, H2.1, H3.1, H4.1, J2.6 (Shield), R5.1
unnamed: C1.2, D1.1 (K), D2.1 (K), JP1.2 (B), R3.1, R4.1, U2.4 (V_{cc})
unnamed: C6.1, Q1.1 (G), Q4.1 (G), R10.1, R11.2
unnamed: C6.2, Q1.2 (S), Q4.2 (S)
unnamed: C11.2, R19.2, R20.1, U6.5 (FB)
unnamed: C17.1, C18.1, U10.1 (CE)
unnamed: C34.2, C35.2
unnamed: C35.1, C36.2, D7.1 (K), D8.2 (A), U12.5 (OV)
unnamed: D3.1 (K), U2.1 (~CHRG)
unnamed: D3.2 (A), R3.2
unnamed: D4.1 (K), U2.5 (~STDBY)
unnamed: D4.2 (A), R4.2
unnamed: D5.2 (A), JP1.1 (A), R11.1
unnamed: D6.2 (A), R27.2
unnamed: D7.2 (A), L3.2, U12.1 (SW)
unnamed: D9.1 (K), R30.2, U12.3 (FB)
unnamed: D10.1 (K), D12.2 (A)
unnamed: D8.1 (K), D10.2 (A)
unnamed: D9.2 (A), D11.1 (K)
unnamed: D11.2 (A), D13.1 (K)
unnamed: D12.1 (K), D14.2 (A)
unnamed: D13.2 (A), D15.1 (K)
unnamed: D14.1 (K), D15.2 (A)
unnamed: J2.1 (VBUS), L1.1, U1.5 (VP)
unnamed: J5.1, U10.6 (OUT2)
unnamed: J5.2, U10.4 (OUT1)
unnamed: JP2.1 (A), Q8.1 (G), R18.2, U5.5 (REL)
unnamed: JP2.2 (B), Q5.1 (G), R12.2
unnamed: L2.1, U6.3 (LX)
unnamed: Q2.3 (D), R8.2, U3.6 (SCL)
unnamed: Q3.3 (D), R9.2, U3.5 (SDA)
unnamed: Q5.3 (D), Q6.1 (G), Q7.3 (D), R13.2, SW1.1, U3.3 (~INT)
unnamed: Q6.3 (D), R16.1, U6.1 (EN)
unnamed: R6.1, R7.1, U2.6 (PROG)
unnamed: R14.2, RV1.1, U5.6 (ONTIME)
unnamed: R17.2, RV2.1, U5.1 (SENS)
unnamed: U3.1 (OSCI), Y1.2
unnamed: U3.2 (OSCO), Y1.1
unnamed: U5.2 (OEN), U7.4 (Q)
VBUS: C3.1, C5.2, C9.1, C28.2, C29.2, C31.2, D5.1 (K), J4.2, L3.1, Q4.3 (D), Q6.2 (S), R8.1, R9.1, R13.1, TP26.1, U3.8 (VDD), U4.3 (VI), U6.4 (IN), U12.6 (VIN)
